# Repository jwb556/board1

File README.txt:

There are 54 SMD placements, with 26 unique parts
There are additionally (3) BOM line items that are TH and would be placed by hand

Assembly Cost Estimate
Quan	Price/Board
3	193
10	75.90
25	33.72
50	19.56
100	12.52
500	6.92
750	6.45

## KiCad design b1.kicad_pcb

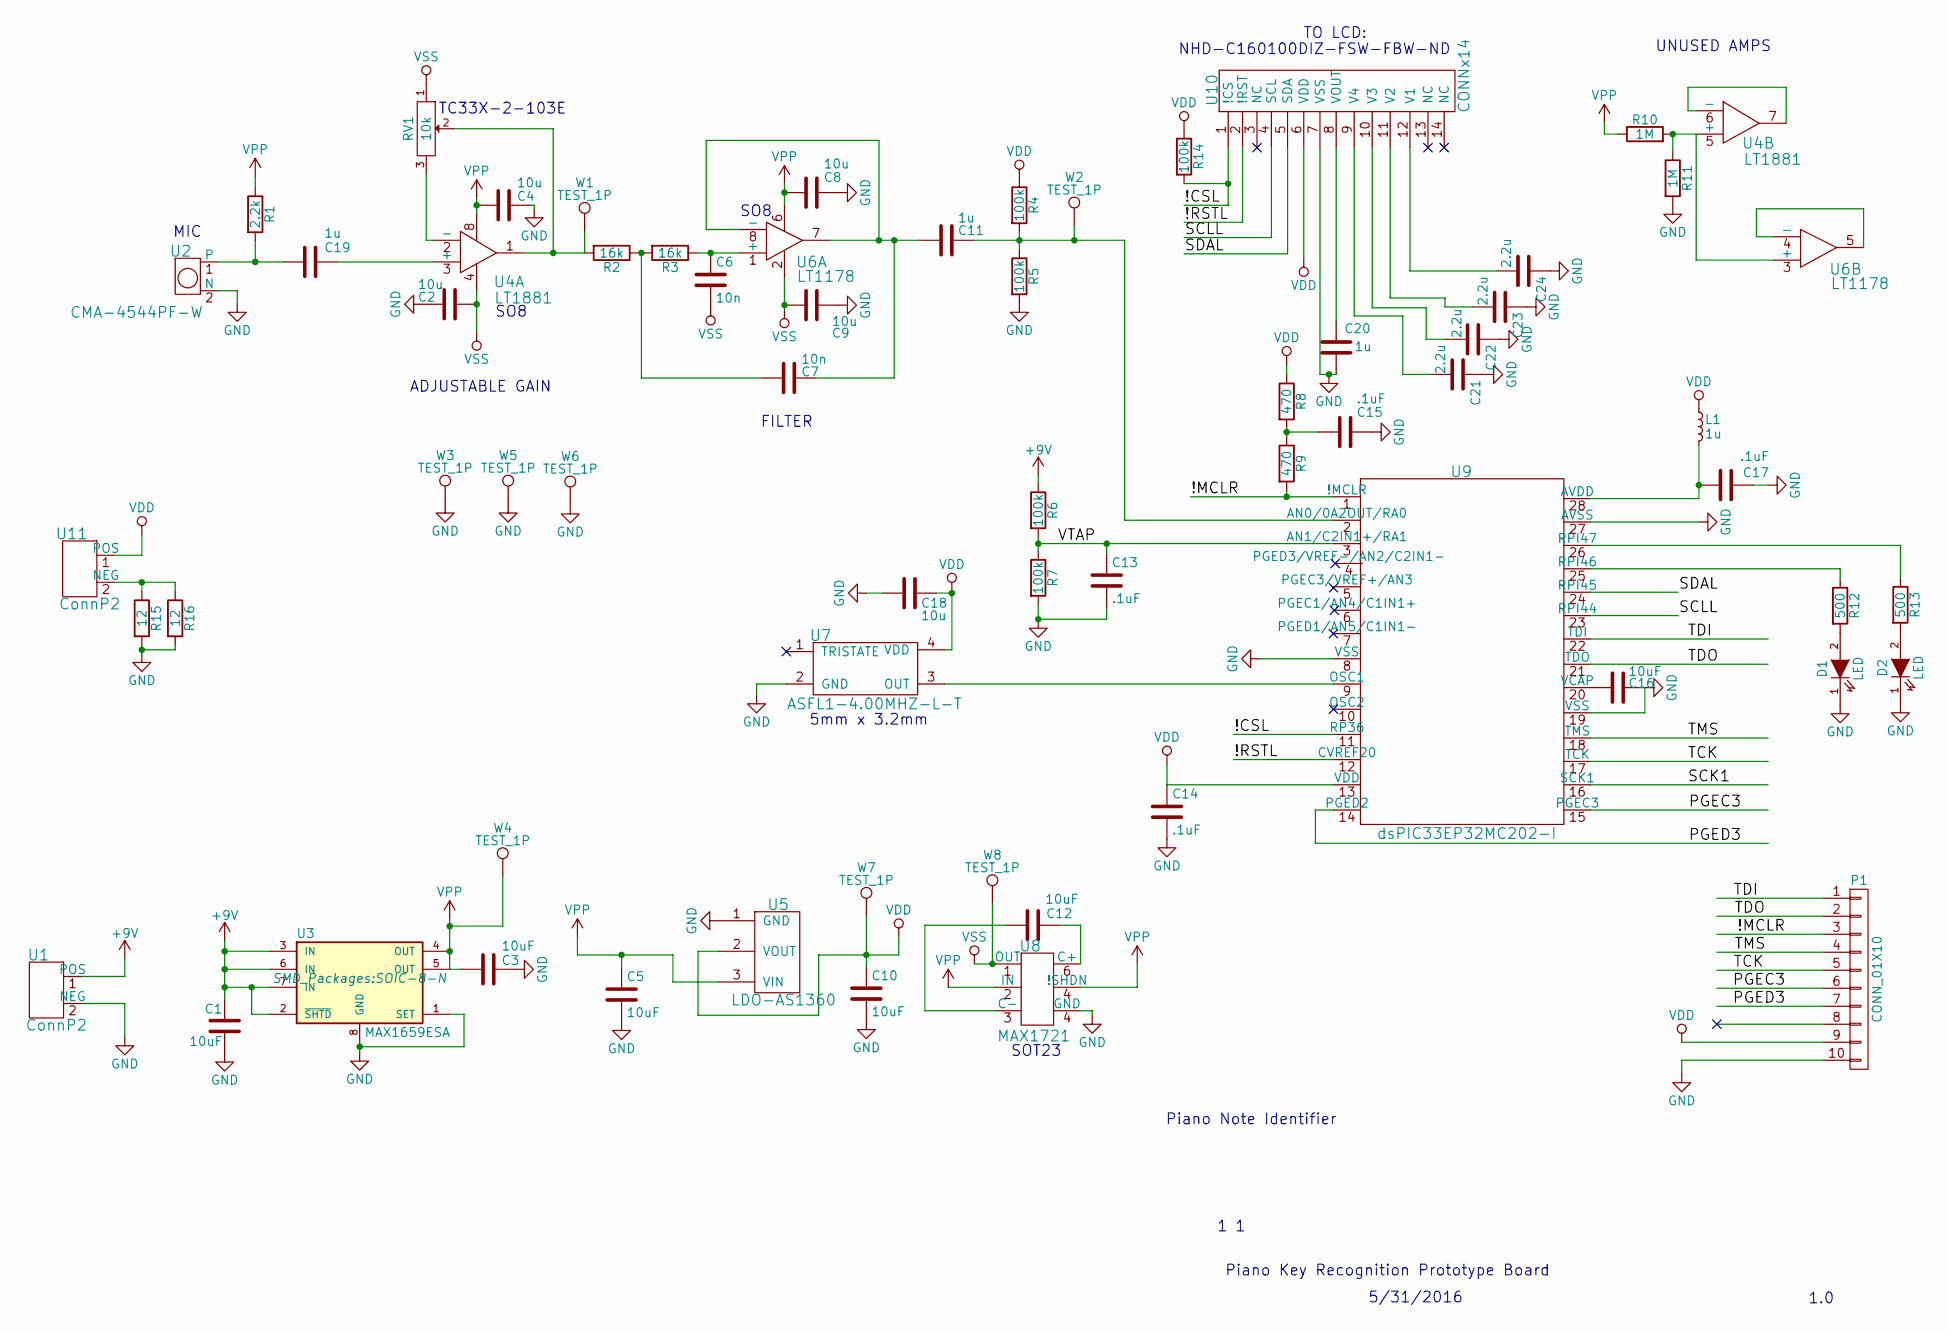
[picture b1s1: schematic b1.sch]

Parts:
C1, C3, C5, C10, C12, C16: 10uF; C_0805_HandSoldering
C2, C4, C8, C9, C18: 10u; C_0805_HandSoldering
C6, C7: 10n; C_0805_HandSoldering
C11, C19, C20: 1u; C_0805_HandSoldering
C13, C14, C15, C17: .1uF; C_0805_HandSoldering
C21, C22, C23, C24: 2.2u; C_0805_HandSoldering
D1, D2: LED; LED_0805
L1: 1u; R_0805
P1: CONN_01X10; CONN_MOLEX_.1IN_2x5
R1: 2.2k; R_0805_HandSoldering
R2, R3: 16k; R_0805_HandSoldering
R4, R5, R6, R7, R14: 100k; R_0805_HandSoldering
R8, R9: 470; R_0805_HandSoldering
R10, R11: 1M; R_0805_HandSoldering
R12, R13: 500; R_0805_HandSoldering
R15, R16: 12; R_0805_HandSoldering
RV1: 10k; POT-TC33X-2-103E
U1: ConnP2; 781710002
U2: CMA-4544PF-W
U3: MAX1659ESA; SOIC-8-N
U4: LT1881; SOIC-8-N
U5: LDO-AS1360; SOT-23
U6: LT1178; SOIC-8-N
U7: ASFL1-4.00MHZ-L-T; ASFL1
U8: MAX1721; SOT-23-6
U9: dsPIC33EP32MC202-I; SOIC28-75
U10: CONNx14; 545482671
U11: ConnP2; JST-SM02B-SRSS-TB
W1, W2, W3, W4, W5, W6, W7, W8: TEST_1P; TESTPOINT-TH-KEYSTONE5118

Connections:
+9V: C1.1, R6.1, U1.1 (POS), U3.2 (~SHTD), U3.3 (IN), U3.6 (IN), U3.7 (IN)
/!CSL: R14.2, U9.11 (RP36), U10.1 (!CS)
/!MCLR: P1.3, R9.2, U9.1 (!MCLR)
/!RSTL: U9.12 (CVREF20), U10.2 (!RST)
/PGEC3: P1.6, U9.15 (PGEC3)
/PGED3: P1.7, U9.14 (PGED2)
/SCLL: U9.23 (RPI44), U10.4 (SCL)
/SDAL: U9.24 (RPI45), U10.5 (SDA)
/TCK: P1.5, U9.17 (TCK)
/TDI: P1.1, U9.22 (TDI)
/TDO: P1.2, U9.21 (TDO)
/TMS: P1.4, U9.18 (TMS)
/VTAP: C13.1, R6.2, R7.1, U9.3 (AN1/C2IN1+/RA1)
unnamed: C6.1, R3.1, U6.1 (+)
unnamed: C7.2, R2.1, R3.2
unnamed: C11.1, R4.2, R5.1, U9.2 (AN0/0A2OUT/RA0), W2.1
unnamed: C7.1, C11.2, U6.7, U6.8 (-)
unnamed: C12.1, U8.6 (C+)
unnamed: C12.2, U8.3 (C-)
unnamed: C15.2, R8.2, R9.1
unnamed: C16.2, U9.20 (VCAP)
unnamed: C17.2, L1.2, U9.28 (AVDD)
unnamed: C19.1, U4.3 (+)
unnamed: C19.2, R1.2, U2.1
unnamed: C20.2, U10.8 (VOUT)
unnamed: C21.2, U10.9 (V4)
unnamed: C22.2, U10.10 (V3)
unnamed: C23.2, U10.11 (V2)
unnamed: C24.2, U10.12 (V1)
unnamed: D1.2 (A), R12.2
unnamed: D2.2 (A), R13.2
unnamed: R2.2, RV1.2, U4.1, W1.1
unnamed: R10.2, R11.1, U4.5 (+), U6.3 (+)
unnamed: R12.1, U9.25 (RPI46)
unnamed: R13.1, U9.26 (RPI47)
unnamed: R15.1, R16.1, U11.2 (NEG)
unnamed: RV1.3, U4.2 (-)
unnamed: U4.6 (-), U4.7
unnamed: U6.4 (-), U6.5
unnamed: U7.3 (OUT), U9.9 (OSC1)
VDD: C10.1, C14.1, C18.1, L1.1, P1.9, R4.1, R8.1, R14.1, U5.2 (VOUT), U7.4 (VDD), U9.13 (VDD), U10.6 (VDD), U11.1 (POS), W7.1
VSS: C2.1, C6.2, C9.2, RV1.1, U4.4, U6.2, U8.1 (OUT), W8.1

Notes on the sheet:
Piano Note Identifier
Piano Key Recognition Prototype Board
UNUSED AMPS
FILTER
ADJUSTABLE GAIN
MIC
5mm x 3.2mm
SOT23
SO8
SO8
TO LCD:
NHD-C160100DIZ-FSW-FBW-ND
1.0
5/31/2016
TC33X-2-103E

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
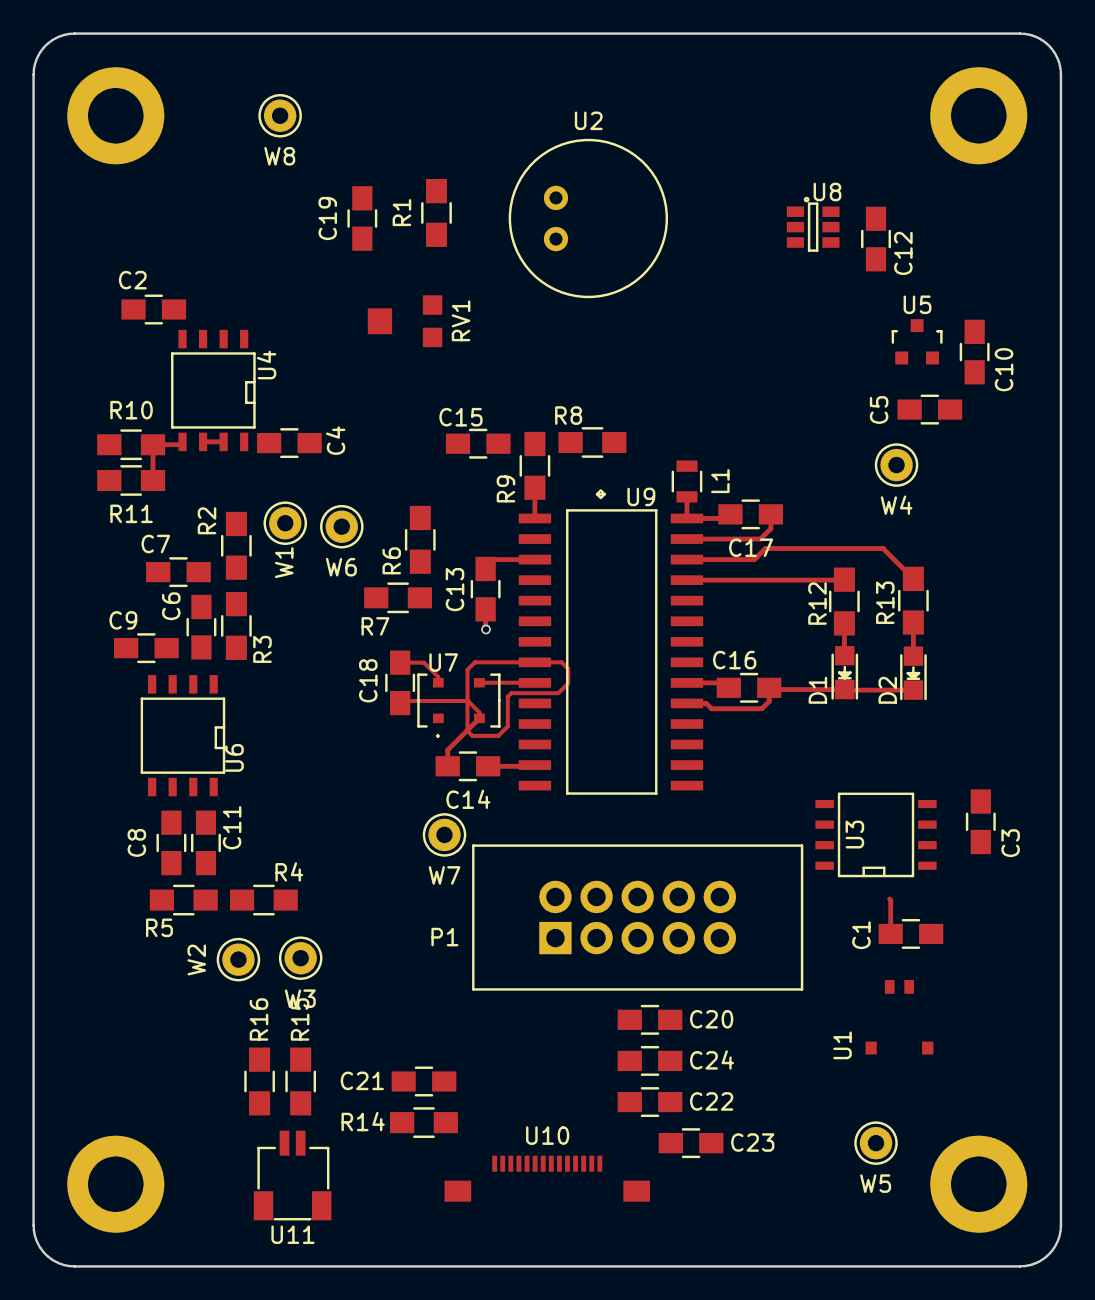
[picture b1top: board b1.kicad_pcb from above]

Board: 2 copper layers, 63.5 x 76.2 mm, 64 parts (0 on the bottom side), 44 nets.

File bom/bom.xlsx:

Id | Designator | Package | Quantity | Designation | Supplier and ref | Price | Quantity | Total
1 | ,,, | 14702 | 4 | 14702
2 | C1,C3,C5,C10,C12,C16 | C_0805_HandSoldering | 6 | 10uF | 399-8013-1-ND | 0.28999999999999998 | 6 | 1.7399999999999998
3 | C2,C4,C8,C9,C18 | C_0805_HandSoldering | 5 | 10u | 399-8013-1-ND | 0.28999999999999998 | 5 | 1.45
4 | C6,C7 | C_0805_HandSoldering | 2 | 10n | 399-7995-1-ND | 0.24 | 2 | 0.48
5 | C11,C19,C20 | C_0805_HandSoldering | 3 | 1u | 399-1284-1-ND | 0.12 | 3 | 0.36
6 | C13,C14,C15,C17 | C_0805_HandSoldering | 4 | .1uF | 399-1167-1-ND | 0.11 | 4 | 0.44
7 | P1 | CONN_MOLEX_.1IN_2x5 | 1 | CONN_01X10 | WM9219-ND | 1.62 | 1 | 1.62
8 | R1 | R_0805_HandSoldering | 1 | 2.2k | 311-2.20KCRCT-ND | 0.1 | 1 | 0.1
9 | R2,R3 | R_0805_HandSoldering | 2 | 16k | P16.0KCCT-ND | 0.1 | 2 | 0.2
10 | R4,R5,R6,R7,R14 | R_0805_HandSoldering | 5 | 100k | P100KCDKR-ND | 0.1 | 5 | 0.5
11 | R8,R9 | R_0805_HandSoldering | 2 | 470 | 311-470ARCT-ND | 0.1 | 2 | 0.2
12 | R10,R11 | R_0805_HandSoldering | 2 | 1M | P1.00MCCT-ND | 0.1 | 2 | 0.2
13 | R12,R13 | R_0805_HandSoldering | 2 | 500 | RNCP0805FTD499RCT-ND | 0.1 | 2 | 0.2
14 | U1 | 781710002 | 1 | ConnP2 | WM4459CT-ND | 0.57999999999999996 | 1 | 0.57999999999999996
15 | U2 | CMA-4544PF-W | 1 | CMA-4544PF-W | 102-1721-ND | 0.96 | 1 | 0.96
16 | U3 | SOIC-8-N | 1 | MAX1659ESA | MAX1659ESA+-ND | 5.73 | 1 | 5.73
17 | U4 | SOIC-8-N | 1 | LT1881 | LT1881CS8#PBF-ND | 5.78 | 1 | 5.78
18 | U5 | SOT-23 | 1 | APE8865N-33-HF-3 | AS1360-50-TCT-ND | 1.41 | 1 | 1.41
19 | U6 | SOIC-8-N | 1 | LT1178 | LT1178S8#PBF-ND | 7.04 | 1 | 7.04
20 | U7 | ASFL1 | 1 | ASFL1-4.00MHZ-L-T | 535-9271-1-ND | 1.77 | 1 | 1.77
21 | U8 | SOT-23-6 | 1 | MAX1721 | MAX1721EUT+T-ND | 0.77 | 1 | 0.77
22 | D1,D2 | LED_0805 | 2 | LED | 160-1423-1-ND | 0.28999999999999998 | 2 | 0.57999999999999996
23 | W1,W2,W3,W4,W5,W6,W7,W8 | TESTPOINT-TH-KEYSTONE5118 | 8 | TEST_1P | 36-5118-ND | 0.37 | 8 | 2.96
24 | L1 | R_0805 | 1 | L_Small | 732-3433-1-ND | 0.92 | 1 | 0.92
25 | U9 | SOIC28-75 | 1 | dsPIC33EP32MC202-I | DSPIC33EP32MC202-I/SS-ND | 1.89 | 1 | 1.89
26 | C21,C22,C23,C24 | C_0805_HandSoldering | 4 | 2.2u | 399-1295-1-ND | 0.17 | 4 | 0.68
27 | U10 | 528921495 | 1 | CONNx14 | WM8835CT-ND | 2.29 | 1 | 2.29
28 | R15,R16 | R_0805_HandSoldering | 2 | 12 | 311-12ARCT-ND | 0.1 | 2 | 0.2
29 | U11 | JST-SM02B-SRSS-TB | 1 | ConnP2 | 455-1802-1-ND | 0.44 | 1 | 0.44
30 | RV1 | POT-TC33X-2-103E | 1 | 10k | TC33X-103ECT-ND | 0.27 | 1 | 0.27
 |  |  |  |  |  |  | TOTAL | 41.760000000000005
) |  |  |  |  |  |  | 64

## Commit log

2016-06-01 Intial commit - Posts have been written on this already.
